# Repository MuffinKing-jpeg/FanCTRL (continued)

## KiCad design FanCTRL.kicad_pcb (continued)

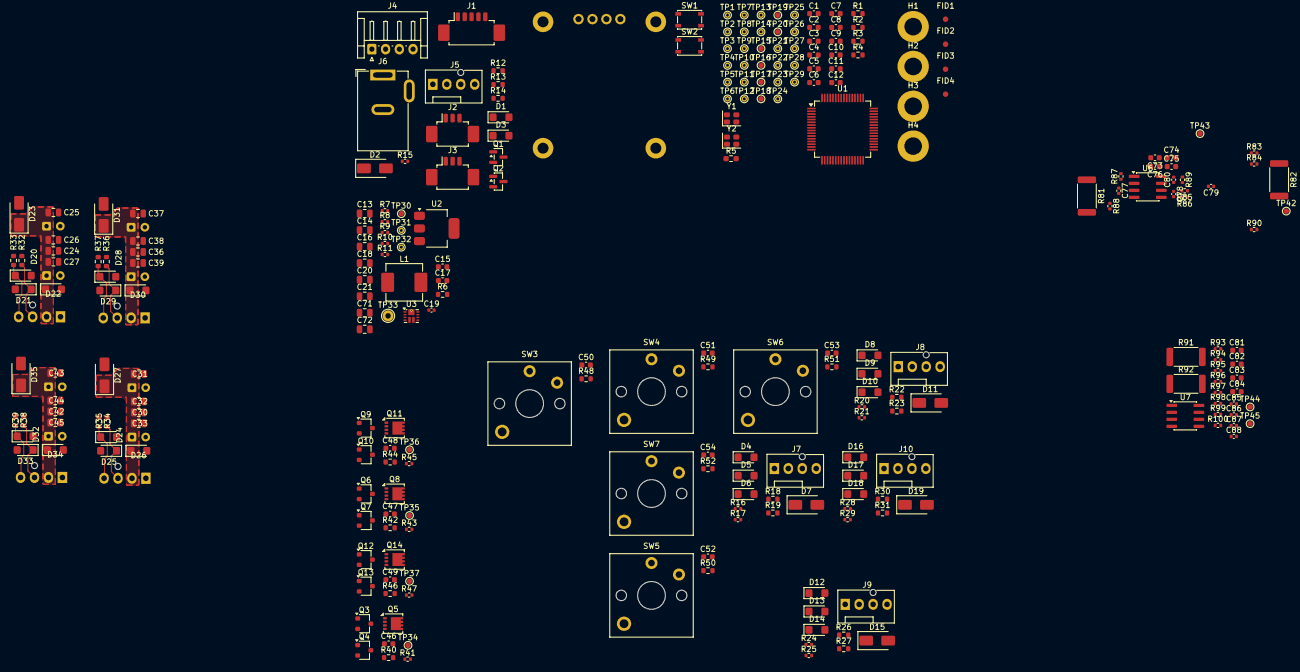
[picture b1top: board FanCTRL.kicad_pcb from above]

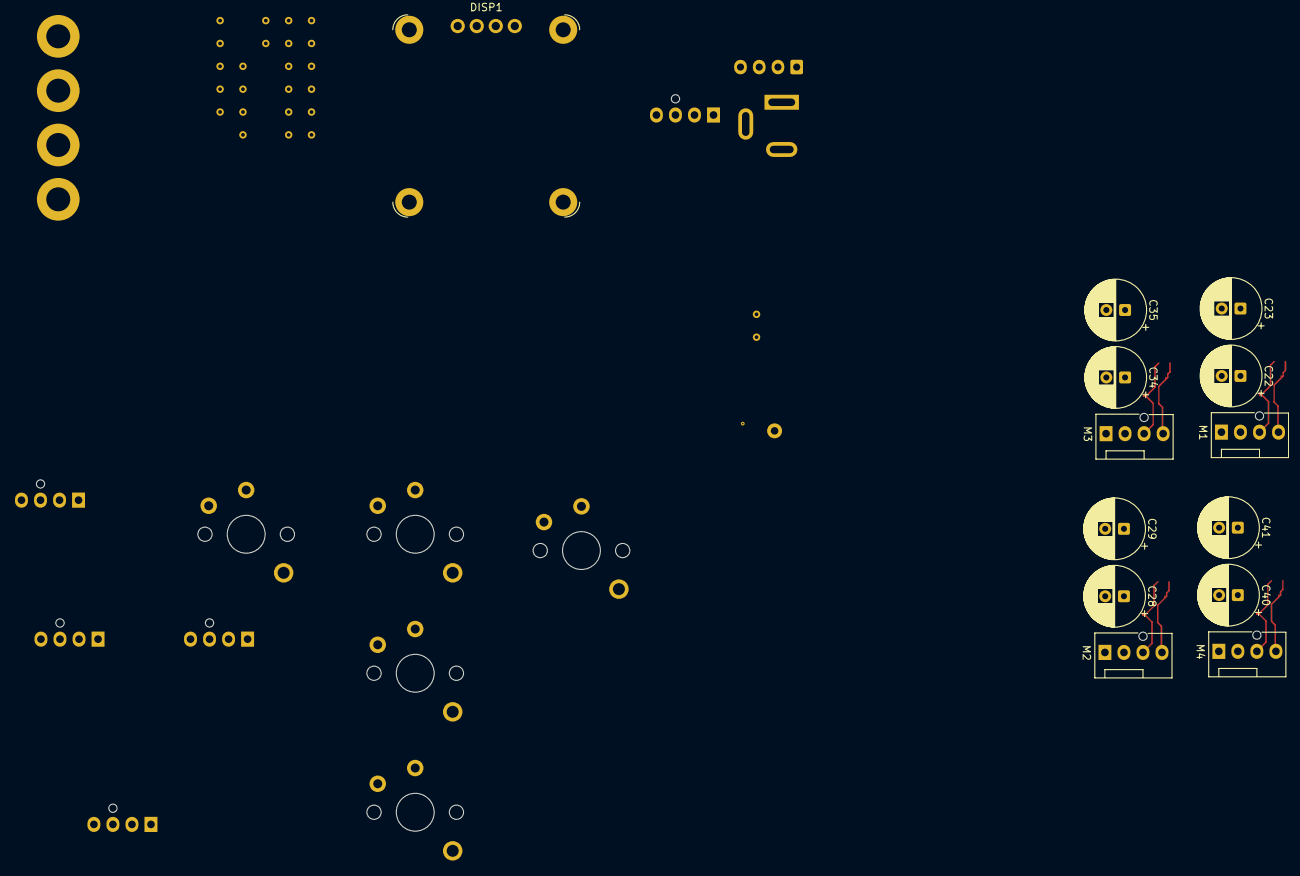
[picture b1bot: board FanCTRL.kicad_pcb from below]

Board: 4 copper layers, 272 parts (13 on the bottom side), 127 nets.

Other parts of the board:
R81, R82: 0.5; R_2512_6332Metric

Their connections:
/Connectors/VOUT3: R81.2; also elsewhere on the board
/Connectors/VOUT4: R82.2; also elsewhere on the board
/Power/OPA2188/IN1: R81.1; also elsewhere on the board
/Power/OPA2188/IN2: R82.1; also elsewhere on the board

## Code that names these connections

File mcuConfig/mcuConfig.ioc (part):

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Mcu.Name=STM32F411R(C-E)Tx
Mcu.Package=LQFP64
Mcu.UserName=STM32F411RETx
PA10.Signal=S_TIM1_CH3
PA11.Signal=S_TIM1_CH4
PA13.Mode=JTAG_4_pins
PA13.Signal=SYS_JTMS-SWDIO
PA14.Mode=JTAG_4_pins
PA14.Signal=SYS_JTCK-SWCLK
PA15.Mode=JTAG_4_pins
PA15.Signal=SYS_JTDI
PA2.Mode=Asynchronous
PA2.Signal=USART2_TX
PA3.Mode=Asynchronous
PA3.Signal=USART2_RX
PA4.GPIOParameters=GPIO_Label
PA4.GPIO_Label=I_CH1
PA4.Signal=ADCx_IN4
PA5.GPIOParameters=GPIO_Label
PA5.GPIO_Label=I_CH2
PA5.Signal=ADCx_IN5
PA6.GPIOParameters=GPIO_Label
PA6.GPIO_Label=I_CH3
PA6.Signal=ADCx_IN6
PA7.GPIOParameters=GPIO_Label
PA7.GPIO_Label=I_CH4
PA7.Signal=ADCx_IN7
PA8.Signal=S_TIM1_CH1
PA9.Signal=S_TIM1_CH2
PB0.GPIOParameters=GPIO_Label
PB0.GPIO_Label=BTN3
PB0.Signal=GPIO_Input
PB1.GPIOParameters=GPIO_Label
PB1.GPIO_Label=BTN4
PB1.Signal=GPIO_Input
PB10.GPIOParameters=GPIO_Label
PB10.GPIO_Label=EN_IN
PB10.Signal=GPIO_Output
PB12.GPIOParameters=GPIO_Label
PB12.GPIO_Label=EN_CH1
PB12.Signal=GPIO_Output
PB13.GPIOParameters=GPIO_Label
PB13.GPIO_Label=EN_CH2
PB13.Signal=GPIO_Output
PB14.GPIOParameters=GPIO_Label
PB14.GPIO_Label=EN_CH3
PB14.Signal=GPIO_Output
PB15.GPIOParameters=GPIO_Label
PB15.GPIO_Label=EN_CH4
PB15.Signal=GPIO_Output
PB2.GPIOParameters=GPIO_Label
PB2.GPIO_Label=BTN5
PB2.Signal=GPIO_Input
PB3.Mode=JTAG_4_pins
PB3.Signal=SYS_JTDO-SWO
PB6.Mode=Asynchronous
PB6.Signal=USART1_TX
PB7.Mode=Asynchronous
PB7.Signal=USART1_RX
PB8.Mode=I2C
PB8.Signal=I2C1_SCL
PB9.Mode=I2C
PB9.Signal=I2C1_SDA
PC0.GPIOParameters=GPIO_Label
PC0.GPIO_Label=U_CH1
PC0.Signal=ADCx_IN10
PC1.GPIOParameters=GPIO_Label
PC1.GPIO_Label=U_CH2
PC1.Signal=ADCx_IN11
PC14-OSC32_IN.Mode=LSE-External-Clock-Source
PC14-OSC32_IN.Signal=RCC_OSC32_IN
PC15-OSC32_OUT.Mode=LSE-External-Clock-Source
PC15-OSC32_OUT.Signal=RCC_OSC32_OUT
PC2.GPIOParameters=GPIO_Label
PC2.GPIO_Label=U_CH3
PC2.Signal=ADCx_IN12
PC3.GPIOParameters=GPIO_Label
PC3.GPIO_Label=U_CH4
PC3.Signal=ADCx_IN13
PC4.GPIOParameters=GPIO_Label
PC4.GPIO_Label=BTN1
PC4.Signal=GPIO_Input
PC5.GPIOParameters=GPIO_Label
PC5.GPIO_Label=BTN2
PC5.Signal=GPIO_Input
PC6.Signal=S_TIM3_CH1
PC7.Signal=S_TIM3_CH2
PC8.Signal=S_TIM3_CH3
PC9.Signal=S_TIM3_CH4
PH0\ -\ OSC_IN.Mode=HSE-External-Clock-Source
PH0\ -\ OSC_IN.Signal=RCC_OSC_IN
PH1\ -\ OSC_OUT.Mode=HSE-External-Clock-Source
PH1\ -\ OSC_OUT.Signal=RCC_OSC_OUT
RCC.HSE_VALUE=8000000
RCC.SYSCLKFreq_VALUE=16000000
board=custom

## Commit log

2026-04-26 Init project
2026-04-26 Added readme.md
